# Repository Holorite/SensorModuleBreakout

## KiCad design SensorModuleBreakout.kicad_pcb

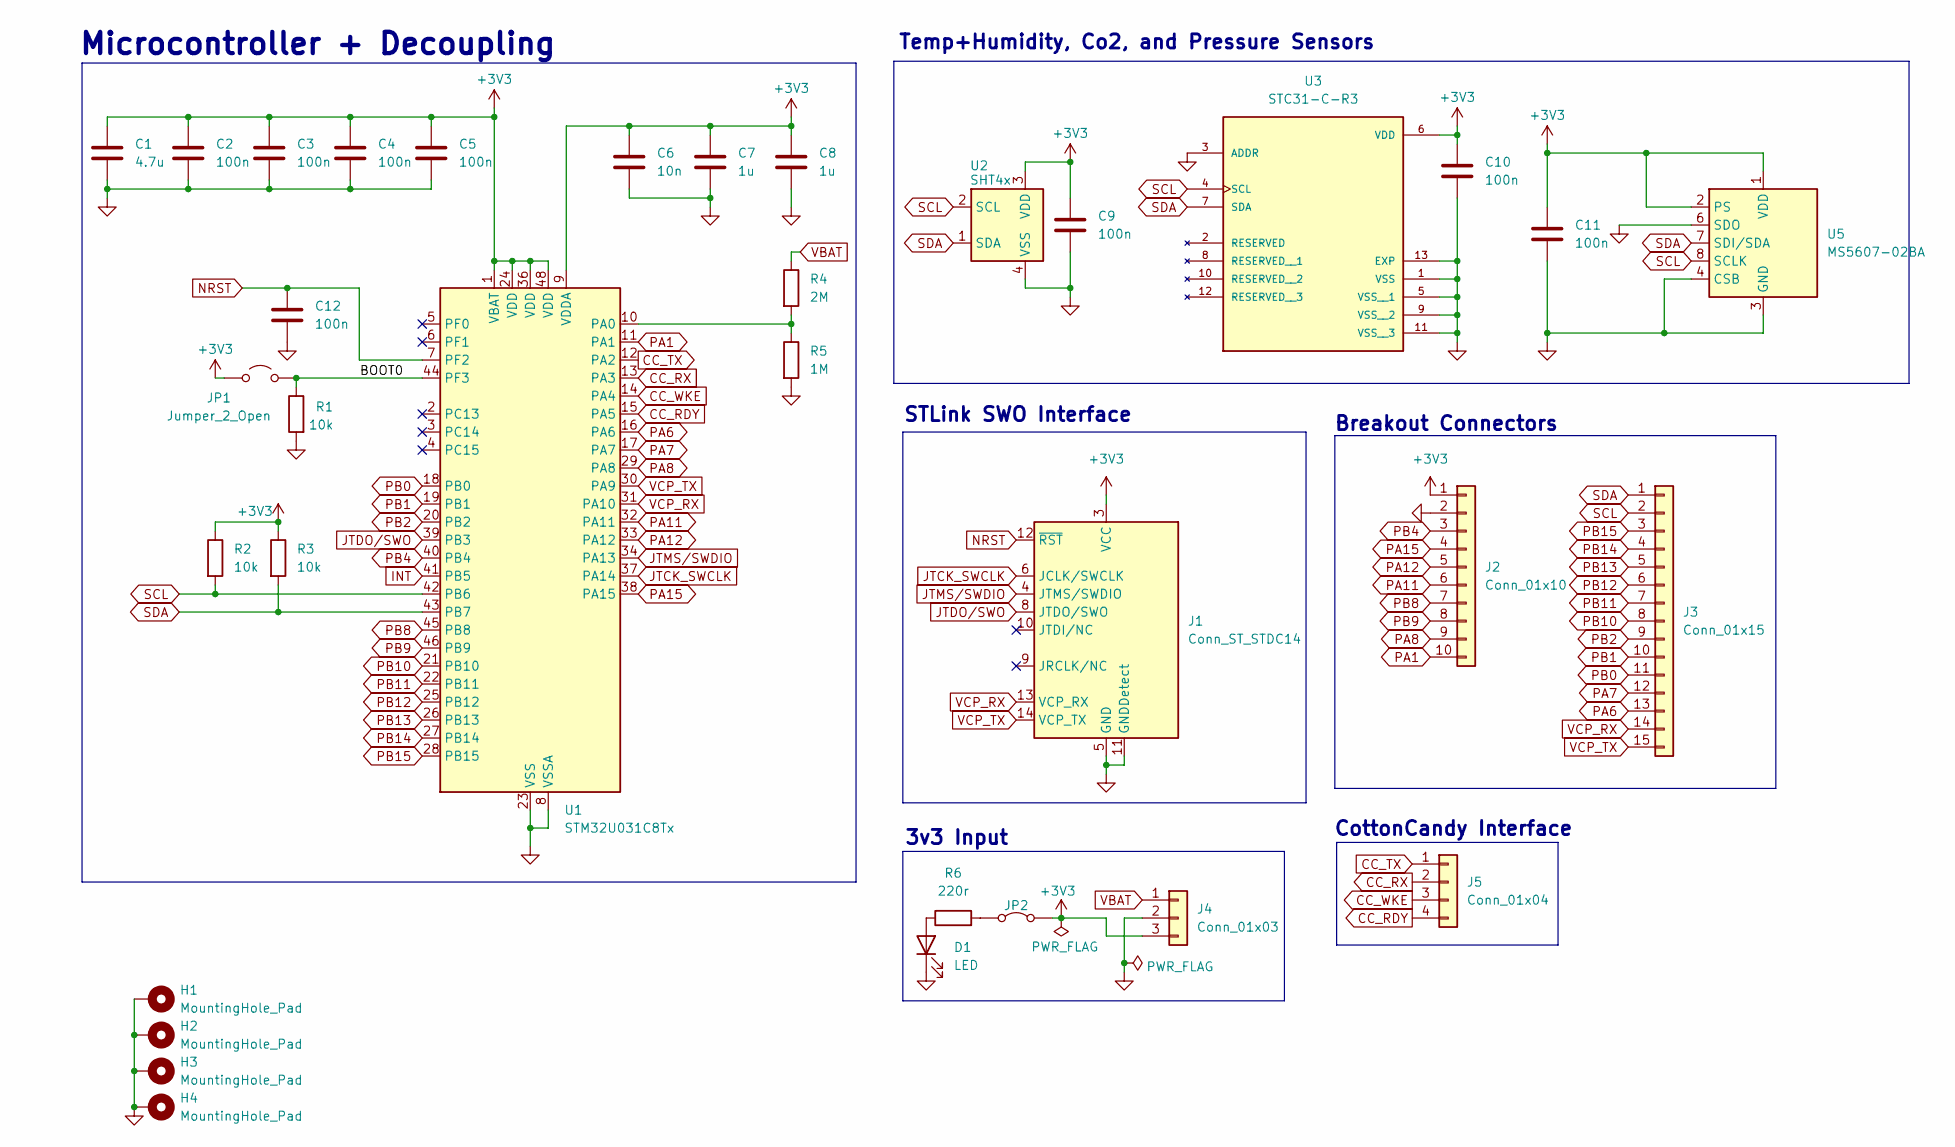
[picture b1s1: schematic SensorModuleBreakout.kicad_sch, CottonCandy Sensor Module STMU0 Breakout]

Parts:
C1: 4.7u; C_0603_1608Metric
C2, C3, C4, C5, C9, C10, C11, C12: 100n; C_0402_1005Metric
C6: 10n; C_0402_1005Metric
C7, C8: 1u; C_0402_1005Metric
D1: LED; LED_0603_1608Metric; JLC C2286
H1, H2, H3, H4: MountingHole_Pad; MountingHole_3.2mm_M3_DIN965_Pad
J1: Conn_ST_STDC14; PinHeader_2x07_P1.27mm_Vertical
J2: Conn_01x10; PinHeader_1x10_P2.54mm_Vertical
J3: Conn_01x15; PinHeader_1x15_P2.54mm_Vertical
J4: Conn_01x03; JST_XH_B3B-XH-A_1x03_P2.50mm_Vertical
J5: Conn_01x04; JST_XH_B4B-XH-A_1x04_P2.50mm_Vertical
JP1: Jumper_2_Open; TestPoint_2Pads_Pitch2.54mm_Drill0.8mm
JP2: JP; TestPoint_2Pads_Pitch2.54mm_Drill0.8mm
R1, R2, R3: 10k; R_0402_1005Metric
R4: 2M; R_0603_1608Metric
R5: 1M; R_0402_1005Metric
R6: 220r; R_0402_1005Metric
U1: STM32U031C8Tx; LQFP-48_7x7mm_P0.5mm
U2: SHT4x; Sensirion_DFN-4_1.5x1.5mm_P0.8mm_SHT4x_NoCentralPad
U3: STC31-C-R3; XDCR_STC31-C-R3; PARTREV 3.2
U5: MS5607-02BA; LGA-8_3x5mm_P1.25mm

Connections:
+3V3: C1.1, C2.1, C3.1, C4.1, C5.1, C6.1, C7.1, C8.1, C9.1, C10.1, C11.1, J1.3 (VCC), J2.1, J4.3, JP1.1 (A), JP2.2 (B), R2.1, R3.1, U1.1 (VBAT), U1.9 (VDDA), U1.24 (VDD), U1.36 (VDD), U1.48 (VDD), U2.3 (VDD), U3.6 (VDD), U5.1 (VDD), U5.2 (PS)
/BOOT0: JP1.2 (B), R1.1, U1.44 (PF3)
CC_RDY: J5.4, U1.15 (PA5)
CC_RX: J5.2, U1.13 (PA3)
CC_TX: J5.1, U1.12 (PA2)
CC_WKE: J5.3, U1.14 (PA4)
GND: C1.2, C2.2, C3.2, C4.2, C5.2, C6.2, C7.2, C8.2, C9.2, C10.2, C11.2, C12.2, D1.1 (K), H1.1, H2.1, H3.1, H4.1, J1.5 (GND), J1.7 (GND), J1.11 (GNDDetect), J2.2, J4.2, R1.2, R5.2, U1.8 (VSSA), U1.23 (VSS), U1.35 (VSS), U1.47 (VSS), U2.4 (VSS), U3.1 (VSS), U3.3 (ADDR), U3.5 (VSS__1), U3.9 (VSS__2), U3.11 (VSS__3), U3.13 (EXP), U5.3 (GND), U5.4 (CSB), U5.5 (CSB), U5.6 (SDO)
JTCK_SWCLK: J1.6 (JCLK/SWCLK), U1.37 (PA14)
JTDO/SWO: J1.8 (JTDO/SWO), U1.39 (PB3)
JTMS/SWDIO: J1.4 (JTMS/SWDIO), U1.34 (PA13)
NRST: C12.1, J1.12 (~RST), U1.7 (PF2)
unnamed: D1.2 (A), R6.1
unnamed: JP2.1 (A), R6.2
unnamed: R4.2, R5.1, U1.10 (PA0)
PA1: J2.10, U1.11 (PA1)
PA6: J3.13, U1.16 (PA6)
PA7: J3.12, U1.17 (PA7)
PA8: J2.9, U1.29 (PA8)
PA11: J2.6, U1.32 (PA11)
PA12: J2.5, U1.33 (PA12)
PA15: J2.4, U1.38 (PA15)
PB0: J3.11, U1.18 (PB0)
PB1: J3.10, U1.19 (PB1)
PB2: J3.9, U1.20 (PB2)
PB4: J2.3, U1.40 (PB4)
PB8: J2.7, U1.45 (PB8)
PB9: J2.8, U1.46 (PB9)
PB10: J3.8, U1.21 (PB10)
PB11: J3.7, U1.22 (PB11)
PB12: J3.6, U1.25 (PB12)
PB13: J3.5, U1.26 (PB13)
PB14: J3.4, U1.27 (PB14)
PB15: J3.3, U1.28 (PB15)
SCL: J3.2, R2.2, U1.42 (PB6), U2.2 (SCL), U3.4 (SCL), U5.8 (SCLK)
SDA: J3.1, R3.2, U1.43 (PB7), U2.1 (SDA), U3.7 (SDA), U5.7 (SDI/SDA)
VBAT: J4.1, R4.1
VCP_RX: J1.13 (VCP_RX), J3.14, U1.31 (PA10)
VCP_TX: J1.14 (VCP_TX), J3.15, U1.30 (PA9)

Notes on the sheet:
Breakout Connectors
3v3 Input
CottonCandy Interface
STLink SWO Interface
Microcontroller + Decoupling
Temp+Humidity, Co2, and Pressure Sensors

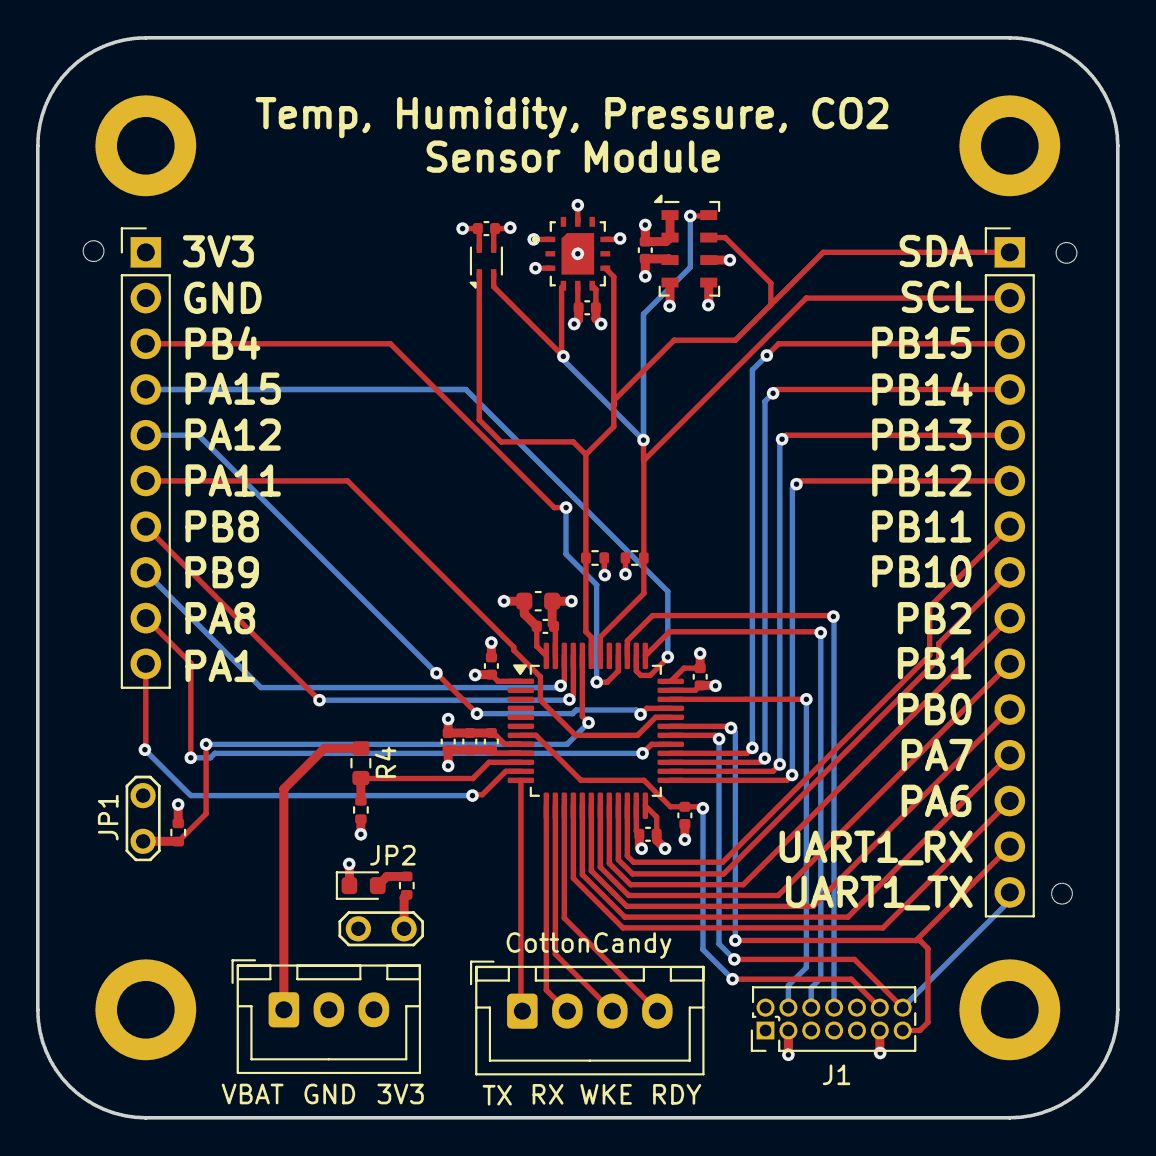
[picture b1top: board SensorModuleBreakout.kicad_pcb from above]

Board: 4 copper layers, 60.0 x 60.0 mm, 34 parts (0 on the bottom side), 38 nets.

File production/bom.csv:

Designator,Footprint,Quantity,Value,LCSC Part #
C1,0603,1,4.7u,C19666
"C10, C11, C12, C2, C3, C4, C5, C9",0402,8,100n,C1525
C6,0402,1,10n,C15195
"C7, C8",0402,2,1u,C52923
D1,0603,1,LED,C2286
"R1, R2, R3",0402,3,10k,C25744
R4,0603,1,2M,C22976
R5,0402,1,1M,C26083
R6,0402,1,220r,C25091
U1,LQFP-48_7x7mm_P0.5mm,1,STM32U031C8Tx,C23172783
U2,Sensirion_DFN-4_1.5x1.5mm_P0.8mm_SHT4x_NoCentralPad,1,SHT4x,C7461861
U3,XDCR_STC31-C-R3,1,STC31-C-R3,C22396918
U4,ST_HLGA-10_2x2mm_P0.5mm_LayoutBorder3x2y,1,LPS22DF,C3253714

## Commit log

2025-02-16 Version 1
2025-02-22 Update production Files for V2
2025-02-22 Fix some rotation errors and minor cleanup
2025-02-23 remove extra fab files
